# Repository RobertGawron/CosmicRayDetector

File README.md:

# CosmicRayDetector

**This project is unfinished.**

## Purpose

Cosmic radiation consists of a constant stream of high-energy particles originating from deep space. When these particles reach Earth, they collide with atoms in the atmosphere, producing a variety of secondary particles, one of which is the muon. This device is designed to detect these muons using a grid of Geiger tubes, while distinguishing them from Earth's natural background radiation. The goal is to create a more precise muon detection system using digital processing, allowing for enhanced readability and further data analysis on a PC, unlike other projects that rely on analog interfaces.

## Principle of Operation

When cosmic rays strike the Earth's atmosphere, they produce high-speed particles, such as muons, which can be detected by Geiger tubes. Due to their high energy, muons pass through Geiger tubes without being stopped, and if multiple tubes are aligned, a muon passing through one will likely pass through others, registering multiple detections. This behavior distinguishes muons from background radiation, which lacks the energy to penetrate multiple Geiger tubes.

To further reduce interference from background radiation, lead shielding is placed around the Geiger tubes. This setup allows the device to filter out low-energy radioactive particles from Earth's environment, isolating the detection of cosmic muons.

## Actual Hardware Version 

The device is the violet PCB. It probably doesn’t work - I can't say for sure because I forgot to buy all the components.

The story behind this device is actually quite interesting. The first version I created was a very small PCB. Depending on which components were soldered, it could be used in three different ways: as a user interface module (with a 4x4 LED grid and push buttons), to connect the GM tube on the "hot side" (connectors and a resistor to limit pulse current), or on the "cold side" (shunt resistor and ADC). It was a clever design to save money on PCB manufacturing, but it added a lot of complexity during assembly. I quickly realized that saving $10 wasn’t worth adding two hours of soldering work.

In the second version, I used NAND gates as an ADC. While I believe this setup would work, it's a bit too old-school, and it would make much more sense to use comparators instead.

The third version is currently under development.

As visible on the image, due to forgetting to buy the NAND gates, as a last resort, I attempted to use a high-to-low logic level converter with MOSFETs I had on hand. It didn’t work, and I didn’t have time to investigate further.

## System Architecture

The user interface is still to be determined.

Tools: PlantUML

## Hardware

* To generate the high voltage required by the Geiger tubes, the [DC/DC converter from this Geiger-Müller counter project](https://github.com/RobertGawron/GeigerMullerCounter) is utilized.
* The Geiger tube model used is the Soviet STS-5 (СТС-5).

Tools: KiCad (for PCB design).

## Software

Software doesn't exists yet.

* The FPGA (Cyclone IV) firmware will be written in Verilog using Quartus Lite as the IDE.
* See [Setting up the development environment on Windows](./wiki/Setting-up-development-environment-on-Windows) for more details.

## Hazards

**Warning: The device operates at high voltage, which can cause serious injury or death. Avoid touching the PCB or Geiger tubes while the device is powered on.**

## License
This project is licensed under the MIT License. See the [LICENSE](./LICENSE) file for details.

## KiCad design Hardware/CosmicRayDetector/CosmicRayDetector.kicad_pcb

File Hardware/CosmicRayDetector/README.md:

# CosmicRayDetector

To reduce manufacturing costs, one PCB was designed all modules. This PCB used in three variants:

- **A/D converter** - four pieces, each for each row of GM Tubes. Mount **only** components visible on  GMTubeConnector.sch, HVConnector.sch
- **Connector between GM tube and high voltage generator** - four pieces, each for ach row of GM Tubes. Mount **only** components visible on **only**  GMTubeConnector.sch, ADC.sch, PowerSupply.sch
- **User interface** - one piece. Mount **only** components visible onUserInterface.sch PowerSupply.sch

In total, nine PCBs are needed.

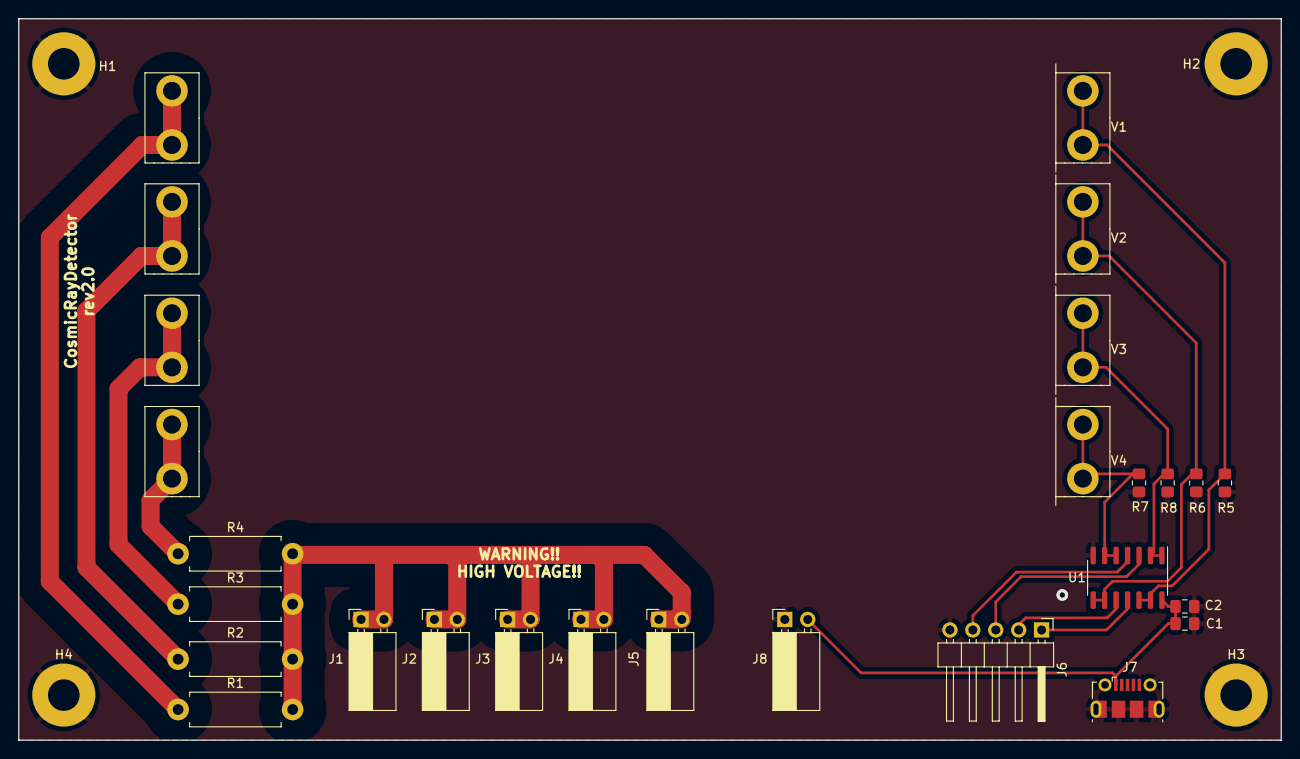
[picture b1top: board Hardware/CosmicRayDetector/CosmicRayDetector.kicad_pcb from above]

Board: 2 copper layers, 140.0 x 80.0 mm, 27 parts (0 on the bottom side), 15 nets.

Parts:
C1, C2: 100n; C_0805_2012Metric_Pad1.18x1.45mm_HandSolder
H1, H2, H3, H4: MountingHole_Pad; MountingHole_3.5mm_Pad
J1, J2, J3, J4, J5, J8: Conn_01x02_Pin; PinSocket_1x02_P2.54mm_Horizontal
J6: Conn_01x05_Socket; PinHeader_1x05_P2.54mm_Horizontal
J7: USB_B_Micro; USB_Micro-B_Molex-105017-0001
R1, R2, R3, R4: 5M1; R_Axial_DIN0411_L9.9mm_D3.6mm_P12.70mm_Horizontal
R5, R6, R7, R8: 10k; R_0805_2012Metric_Pad1.20x1.40mm_HandSolder
U1: HEF4093B; SOIC-14_3.9x8.7mm_P1.27mm
V1, V2, V3, V4: Nuclear-Radiation_Detector; GeigerTube

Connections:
+5V: C1.1, C2.1, J7.1 (VBUS), J8.2, U1.14 (VCC)
GND: C1.2, C2.2, H1.1, H2.1, H3.1, H4.1, J6.5, J7.5 (GND), J7.6 (Shield), J8.1, R5.2, R6.2, R7.2, R8.2, U1.7 (GND)
unnamed: J1.1, J1.2, J2.1, J2.2, J3.1, J3.2, J4.1, J4.2, J5.1, J5.2, R1.2, R2.2, R3.2, R4.2
unnamed: J6.1, U1.11
unnamed: J6.2, U1.10
unnamed: J6.3, U1.3
unnamed: J6.4, U1.4
unnamed: R1.1, V1.2
unnamed: R2.1, V2.2
unnamed: R3.1, V3.2
unnamed: R4.1, V4.2
unnamed: R5.1, U1.12, U1.13, V1.1
unnamed: R6.1, U1.8, U1.9, V2.1
unnamed: R7.1, U1.5, U1.6, V4.1
unnamed: R8.1, U1.1, U1.2, V3.1

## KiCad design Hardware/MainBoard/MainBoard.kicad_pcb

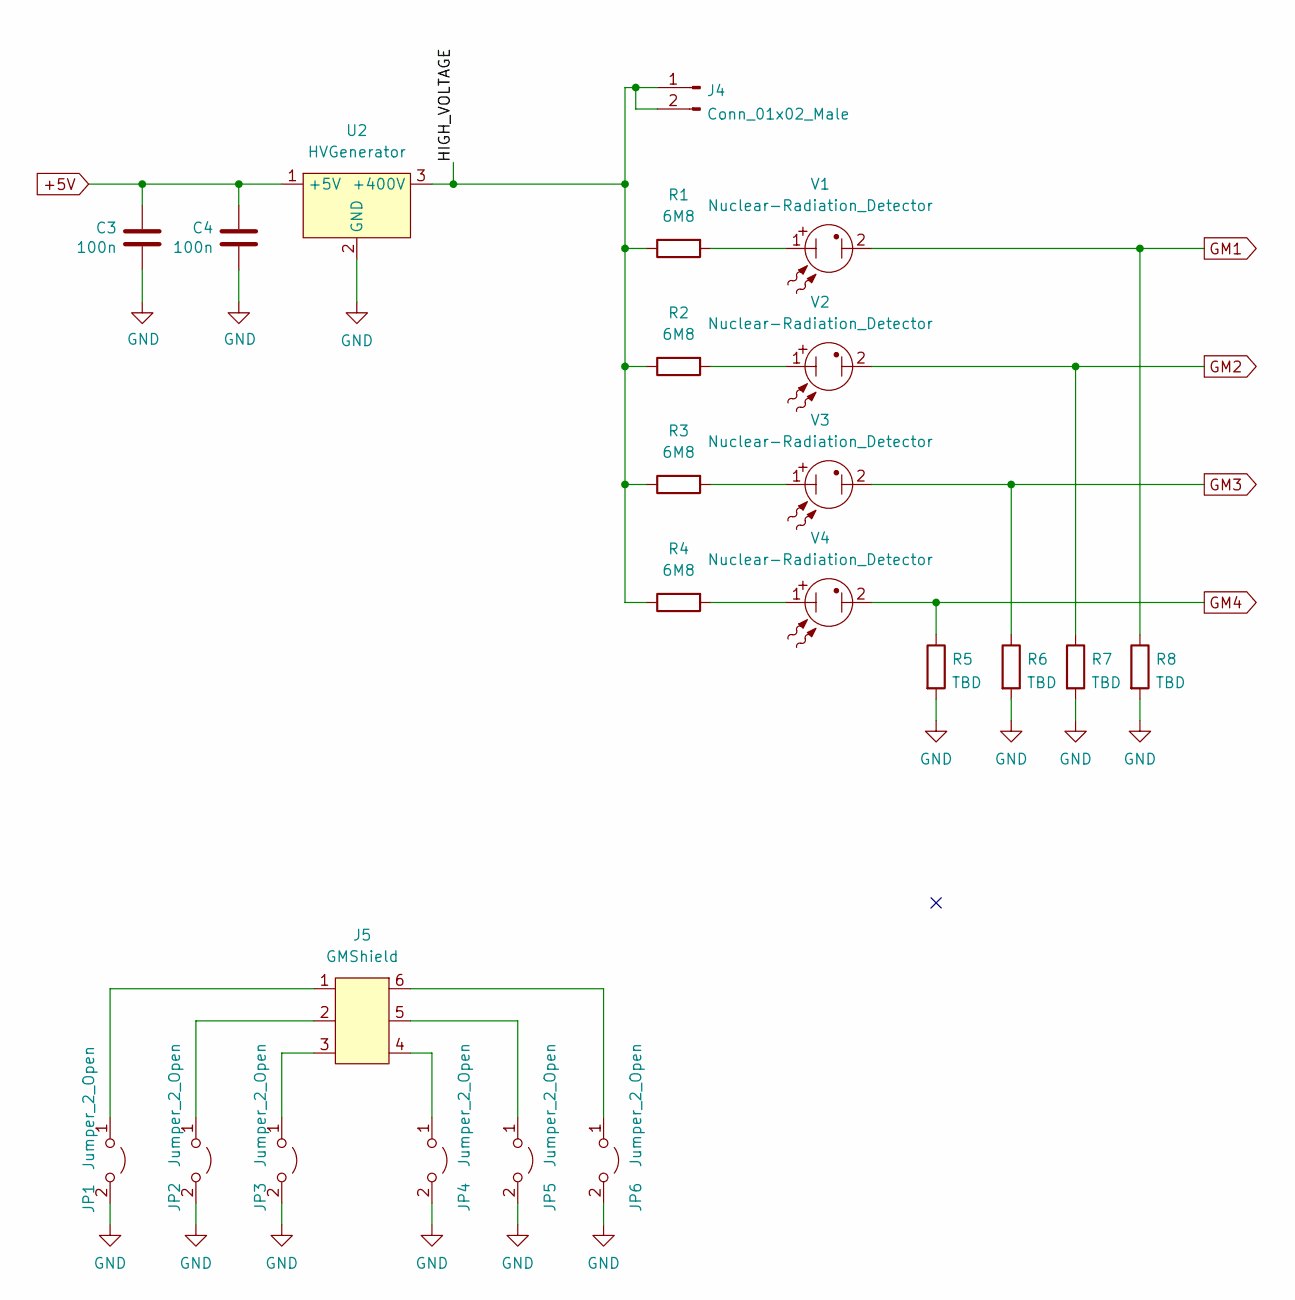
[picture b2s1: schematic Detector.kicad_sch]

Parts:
C3, C4: 100n; C_0805_2012Metric
J4: Conn_01x02_Male; PinHeader_1x02_P2.54mm_Horizontal
J5: GMShield
JP1, JP2, JP3, JP4, JP5, JP6: Jumper_2_Open; SolderJumper-2_P1.3mm_Open_Pad1.0x1.5mm
R1, R2, R3, R4: 6M8; R_Axial_DIN0207_L6.3mm_D2.5mm_P10.16mm_Horizontal
R5, R6, R7, R8: TBD; R_0805_2012Metric
U2: HVGenerator
V1, V2, V3, V4: Nuclear-Radiation_Detector; GeigerTubeConnector

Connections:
+5V: C3.1, C4.1, U2.1 (+5V); also elsewhere on the board
/Detector/HIGH_VOLTAGE: J4.1, J4.2, R1.1, R2.1, R3.1, R4.1, U2.3 (+400V)
GM1: R8.1, V1.2; also elsewhere on the board
GM2: R7.1, V2.2; also elsewhere on the board
GM3: R6.1, V3.2; also elsewhere on the board
GM4: R5.1, V4.2; also elsewhere on the board
GND: C3.2, C4.2, JP1.2 (B), JP2.2 (B), JP3.2 (B), JP4.2 (B), JP5.2 (B), JP6.2 (B), R5.2, R6.2, R7.2, R8.2, U2.2 (GND); also elsewhere on the board
unnamed: J5.1, JP1.1 (A)
unnamed: J5.2, JP2.1 (A)
unnamed: J5.3, JP3.1 (A)
unnamed: J5.4, JP4.1 (A)
unnamed: J5.5, JP5.1 (A)
unnamed: J5.6, JP6.1 (A)
unnamed: R1.2, V1.1
unnamed: R2.2, V2.1
unnamed: R3.2, V3.1
unnamed: R4.2, V4.1

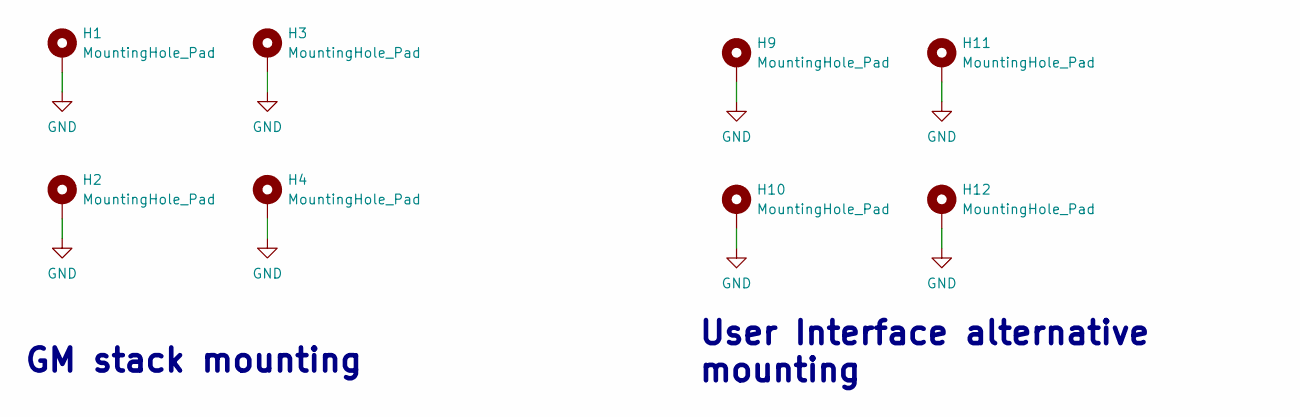
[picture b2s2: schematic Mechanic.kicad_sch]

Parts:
H1, H2, H3, H4, H9, H10, H11, H12: MountingHole_Pad; MountingHole_3.2mm_M3_DIN965_Pad

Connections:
GND: H1.1, H2.1, H3.1, H4.1, H9.1, H10.1, H11.1, H12.1; also elsewhere on the board

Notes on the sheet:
GM stack mounting
User Interface alternative mounting

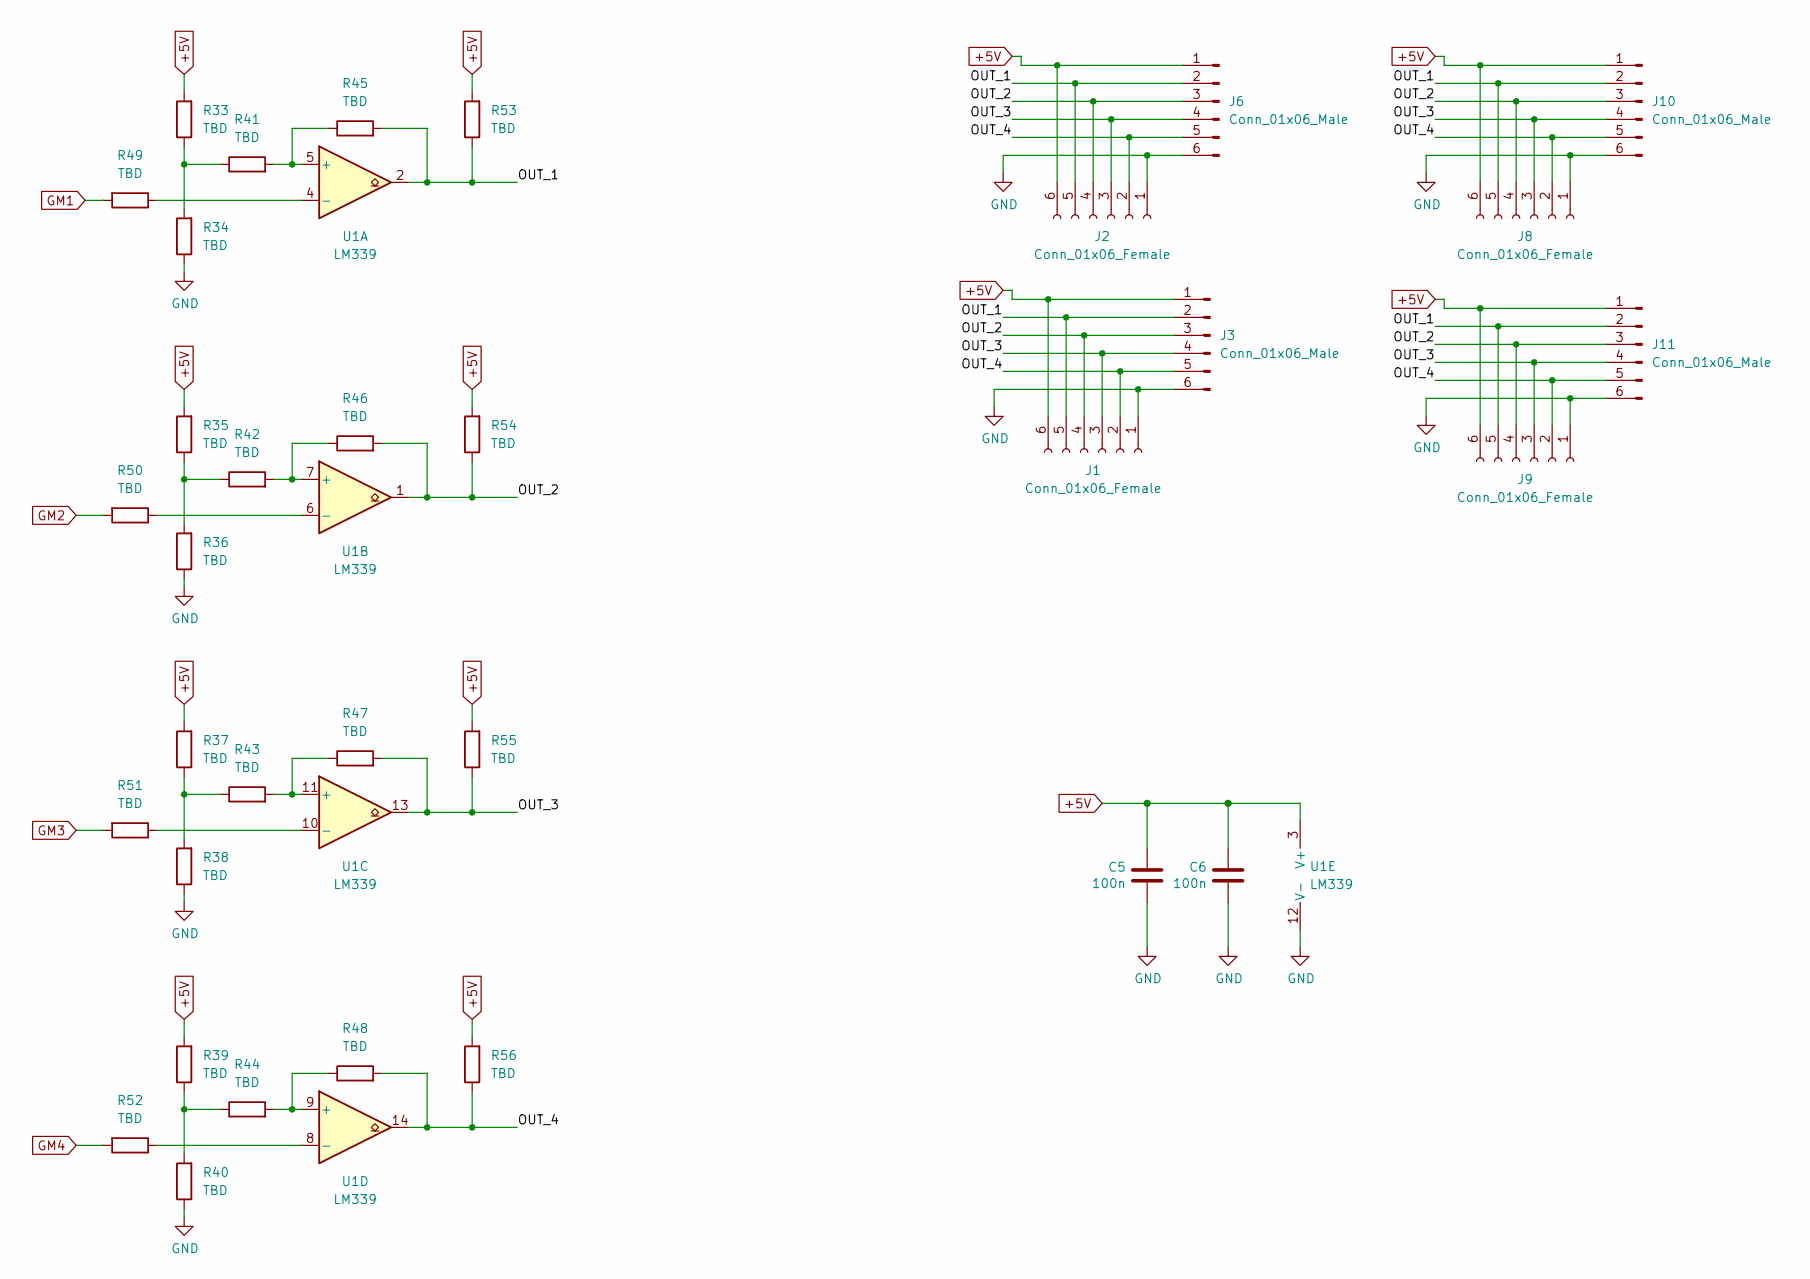
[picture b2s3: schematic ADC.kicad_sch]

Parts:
C5, C6: 100n; C_0805_2012Metric
J1, J2, J8, J9: Conn_01x06_Female; PinSocket_1x06_P2.54mm_Vertical_SMD_Pin1Left
J3, J6, J10, J11: Conn_01x06_Male; PinHeader_1x06_P2.54mm_Vertical_SMD_Pin1Left
R33, R34, R35, R36, R37, R38, R39, R40, R41, R42, R43, R44, R45, R46, R47, R48, R49, R50, R51, R52, R53, R54, R55, R56: TBD; R_0805_2012Metric
U1: LM339; SO-14_3.9x8.65mm_P1.27mm

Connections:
+5V: C5.1, C6.1, J1.6, J2.6, J3.1, J6.1, J8.6, J9.6, J10.1, J11.1, R33.2, R35.2, R37.2, R39.2, R53.2, R54.2, R55.2, R56.2, U1.3 (V+); also elsewhere on the board
/ADC/OUT_1: J1.5, J2.5, J3.2, J6.2, J8.5, J9.5, J10.2, J11.2, R45.2, R53.1, U1.2
/ADC/OUT_2: J1.4, J2.4, J3.3, J6.3, J8.4, J9.4, J10.3, J11.3, R46.2, R54.1, U1.1
/ADC/OUT_3: J1.3, J2.3, J3.4, J6.4, J8.3, J9.3, J10.4, J11.4, R47.2, R55.1, U1.13
/ADC/OUT_4: J1.2, J2.2, J3.5, J6.5, J8.2, J9.2, J10.5, J11.5, R48.2, R56.1, U1.14
GM1: R49.2; also elsewhere on the board
GM2: R50.2; also elsewhere on the board
GM3: R51.2; also elsewhere on the board
GM4: R52.2; also elsewhere on the board
GND: C5.2, C6.2, J1.1, J2.1, J3.6, J6.6, J8.1, J9.1, J10.6, J11.6, R34.1, R36.1, R38.1, R40.1, U1.12 (V-); also elsewhere on the board
unnamed: R33.1, R34.2, R41.1
unnamed: R35.1, R36.2, R42.1
unnamed: R37.1, R38.2, R43.1
unnamed: R39.1, R40.2, R44.1
unnamed: R49.1, U1.4 (-)
unnamed: R41.2, R45.1, U1.5 (+)
unnamed: R50.1, U1.6 (-)
unnamed: R42.2, R46.1, U1.7 (+)
unnamed: R52.1, U1.8 (-)
unnamed: R44.2, R48.1, U1.9 (+)
unnamed: R51.1, U1.10 (-)
unnamed: R43.2, R47.1, U1.11 (+)

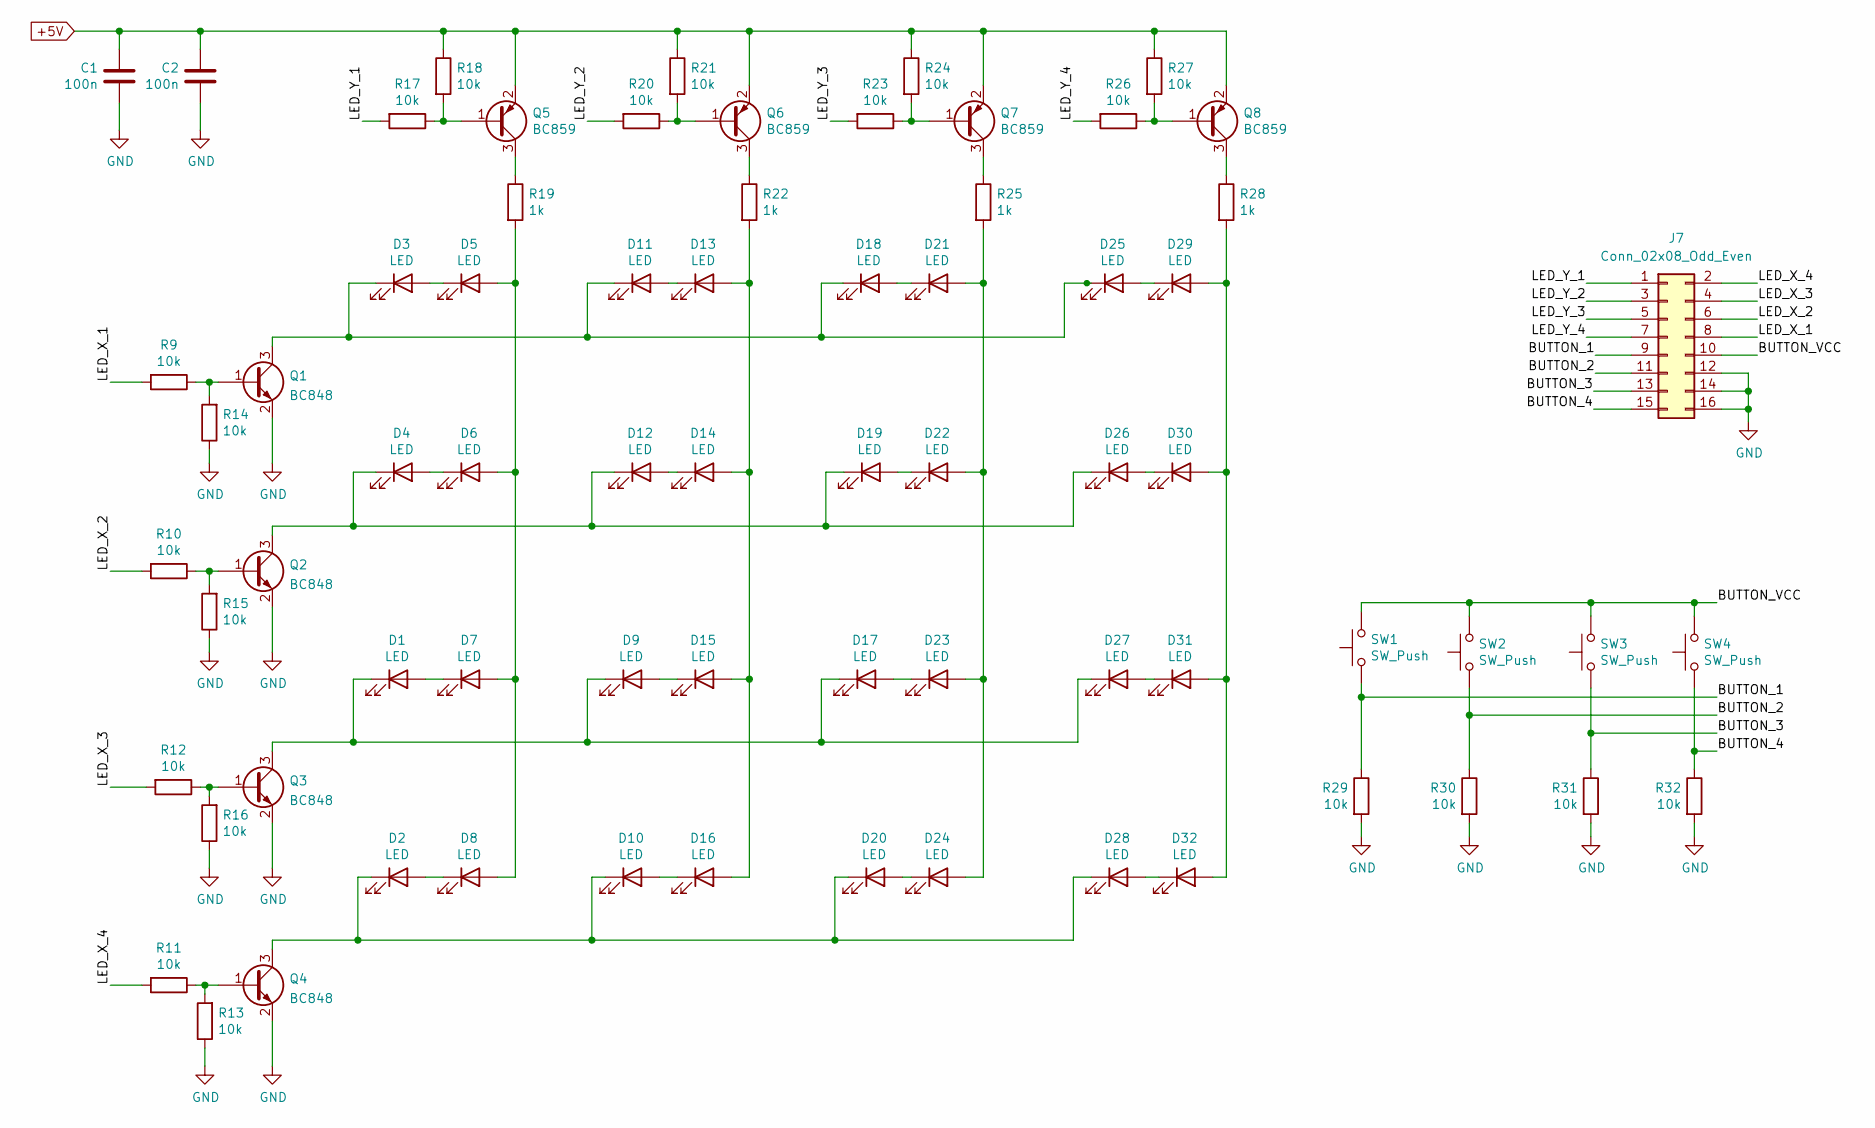
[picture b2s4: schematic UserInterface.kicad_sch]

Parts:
C1, C2: 100n; C_0805_2012Metric
D1, D2, D3, D4, D5, D6, D7, D8, D9, D10, D11, D12, D13, D14, D15, D16, D17, D18, D19, D20, D21, D22, D23, D24, D25, D26, D27, D28, D29, D30, D31, D32: LED; LED_1206_3216Metric
J7: Conn_02x08_Odd_Even; PinHeader_2x08_P2.54mm_Vertical
Q1, Q2, Q3, Q4: BC848; SOT-23
Q5, Q6, Q7, Q8: BC859; SOT-23
R9, R10, R11, R12, R13, R14, R15, R16, R17, R18, R20, R21, R23, R24, R26, R27, R29, R30, R31, R32: 10k; R_0805_2012Metric
R19, R22, R25, R28: 1k; R_0805_2012Metric
SW1, SW2, SW3, SW4: SW_Push; SW_PUSH_6mm

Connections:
+5V: C1.1, C2.1, Q5.2 (E), Q6.2 (E), Q7.2 (E), Q8.2 (E), R18.1, R21.1, R24.1, R27.1; also elsewhere on the board
/UserInterface/BUTTON_1: J7.9, R29.1, SW1.1
/UserInterface/BUTTON_2: J7.11, R30.1, SW2.1
/UserInterface/BUTTON_3: J7.13, R31.1, SW3.1
/UserInterface/BUTTON_4: J7.15, R32.1, SW4.1
/UserInterface/BUTTON_VCC: J7.10, SW1.2, SW2.2, SW3.2, SW4.2
/UserInterface/LED_X_1: J7.8, R9.2
/UserInterface/LED_X_2: J7.6, R10.2
/UserInterface/LED_X_3: J7.4, R12.2
/UserInterface/LED_X_4: J7.2, R11.2
/UserInterface/LED_Y_1: J7.1, R17.2
/UserInterface/LED_Y_2: J7.3, R20.2
/UserInterface/LED_Y_3: J7.5, R23.2
/UserInterface/LED_Y_4: J7.7, R26.2
GND: C1.2, C2.2, J7.12, J7.14, J7.16, Q1.2 (E), Q2.2 (E), Q3.2 (E), Q4.2 (E), R13.1, R14.1, R15.1, R16.1, R29.2, R30.2, R31.2, R32.2; also elsewhere on the board
unnamed: D1.1 (K), D9.1 (K), D17.1 (K), D27.1 (K), Q3.3 (C)
unnamed: D1.2 (A), D7.1 (K)
unnamed: D2.2 (A), D8.1 (K)
unnamed: D3.2 (A), D5.1 (K)
unnamed: D4.2 (A), D6.1 (K)
unnamed: D5.2 (A), D6.2 (A), D7.2 (A), D8.2 (A), R19.2
unnamed: D2.1 (K), D10.1 (K), D20.1 (K), D28.1 (K), Q4.3 (C)
unnamed: D10.2 (A), D16.1 (K)
unnamed: D3.1 (K), D11.1 (K), D18.1 (K), D25.1 (K), Q1.3 (C)
unnamed: D11.2 (A), D13.1 (K)
unnamed: D4.1 (K), D12.1 (K), D19.1 (K), D26.1 (K), Q2.3 (C)
unnamed: D12.2 (A), D14.1 (K)
unnamed: D13.2 (A), D14.2 (A), D15.2 (A), D16.2 (A), R22.2
unnamed: D9.2 (A), D15.1 (K)
unnamed: D17.2 (A), D23.1 (K)
unnamed: D18.2 (A), D21.1 (K)
unnamed: D19.2 (A), D22.1 (K)
unnamed: D20.2 (A), D24.1 (K)
unnamed: D21.2 (A), D22.2 (A), D23.2 (A), D24.2 (A), R25.2
unnamed: D25.2 (A), D29.1 (K)
unnamed: D26.2 (A), D30.1 (K)
unnamed: D27.2 (A), D31.1 (K)
unnamed: D28.2 (A), D32.1 (K)
unnamed: D29.2 (A), D30.2 (A), D31.2 (A), D32.2 (A), R28.2
unnamed: Q1.1 (B), R9.1, R14.2
unnamed: Q2.1 (B), R10.1, R15.2
unnamed: Q3.1 (B), R12.1, R16.2
unnamed: Q4.1 (B), R11.1, R13.2
unnamed: Q5.1 (B), R17.1, R18.2
unnamed: Q5.3 (C), R19.1
unnamed: Q6.1 (B), R20.1, R21.2
unnamed: Q6.3 (C), R22.1
unnamed: Q7.1 (B), R23.1, R24.2
unnamed: Q7.3 (C), R25.1
unnamed: Q8.1 (B), R26.1, R27.2
unnamed: Q8.3 (C), R28.1

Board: 2 copper layers, 137 parts (0 on the bottom side), 82 nets, no tracks yet.

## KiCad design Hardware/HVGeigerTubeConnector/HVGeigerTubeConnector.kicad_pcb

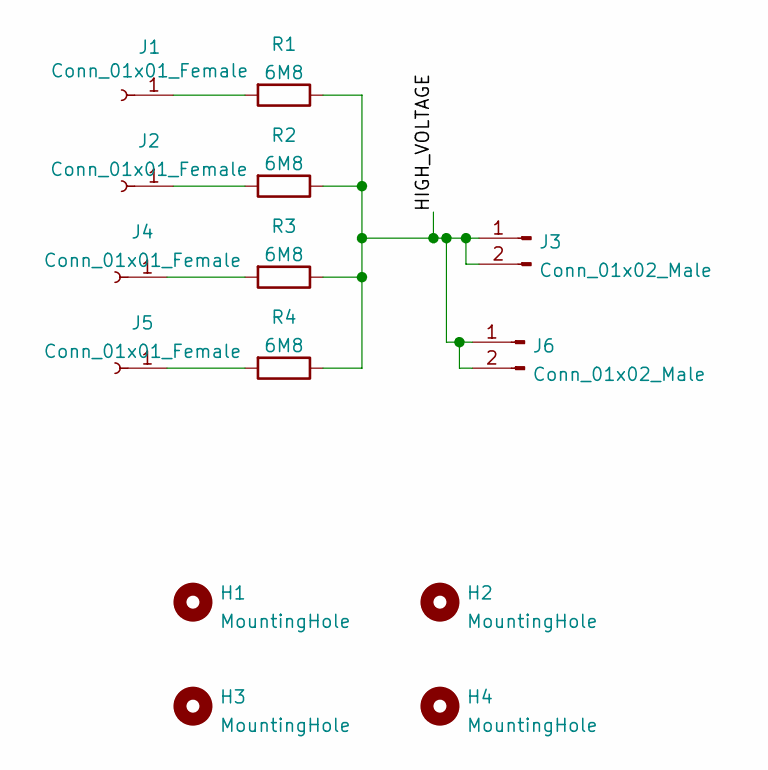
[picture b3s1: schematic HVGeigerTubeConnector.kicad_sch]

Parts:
H1, H2, H3, H4: MountingHole; MountingHole_3.5mm
J1, J2, J4, J5: Conn_01x01_Female; GeigerTubeConnector
J3, J6: Conn_01x02_Male; PinHeader_1x02_P2.54mm_Horizontal
R1, R2, R3, R4: 6M8; R_Axial_DIN0207_L6.3mm_D2.5mm_P10.16mm_Horizontal

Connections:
/HIGH_VOLTAGE: J3.1, J3.2, J6.1, J6.2, R1.1, R2.1, R3.1, R4.1
unnamed: J1.1, R1.2
unnamed: J2.1, R2.2
unnamed: J4.1, R3.2
unnamed: J5.1, R4.2

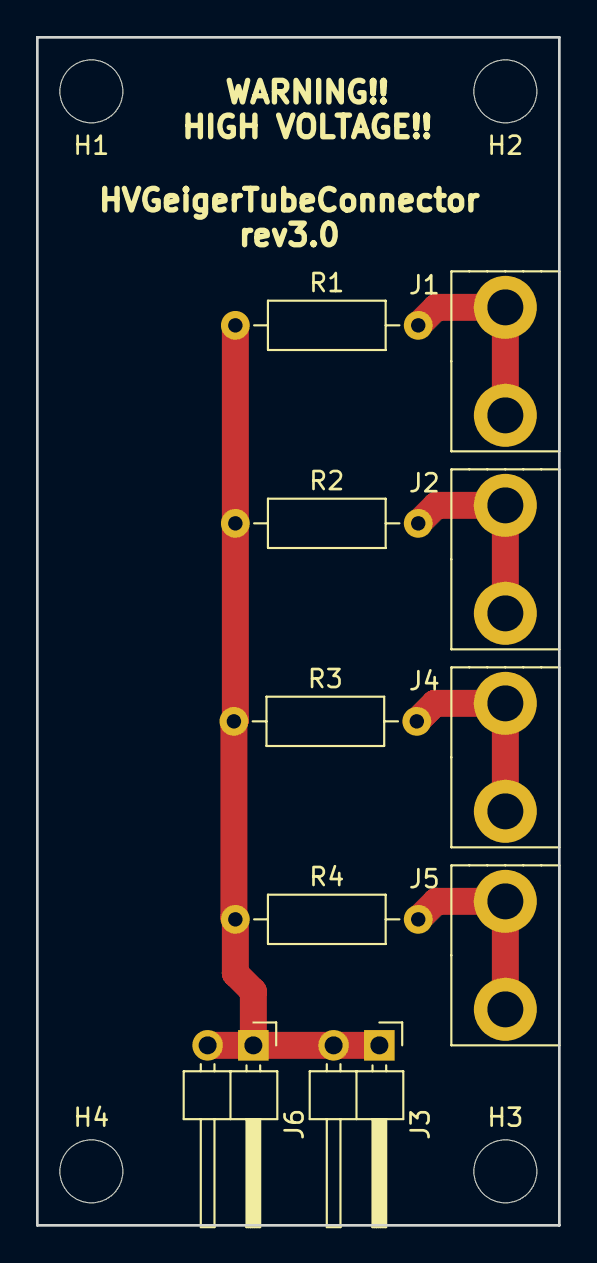
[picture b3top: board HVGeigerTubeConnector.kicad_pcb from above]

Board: 2 copper layers, 29.0 x 66.0 mm, 14 parts (0 on the bottom side), 5 nets.

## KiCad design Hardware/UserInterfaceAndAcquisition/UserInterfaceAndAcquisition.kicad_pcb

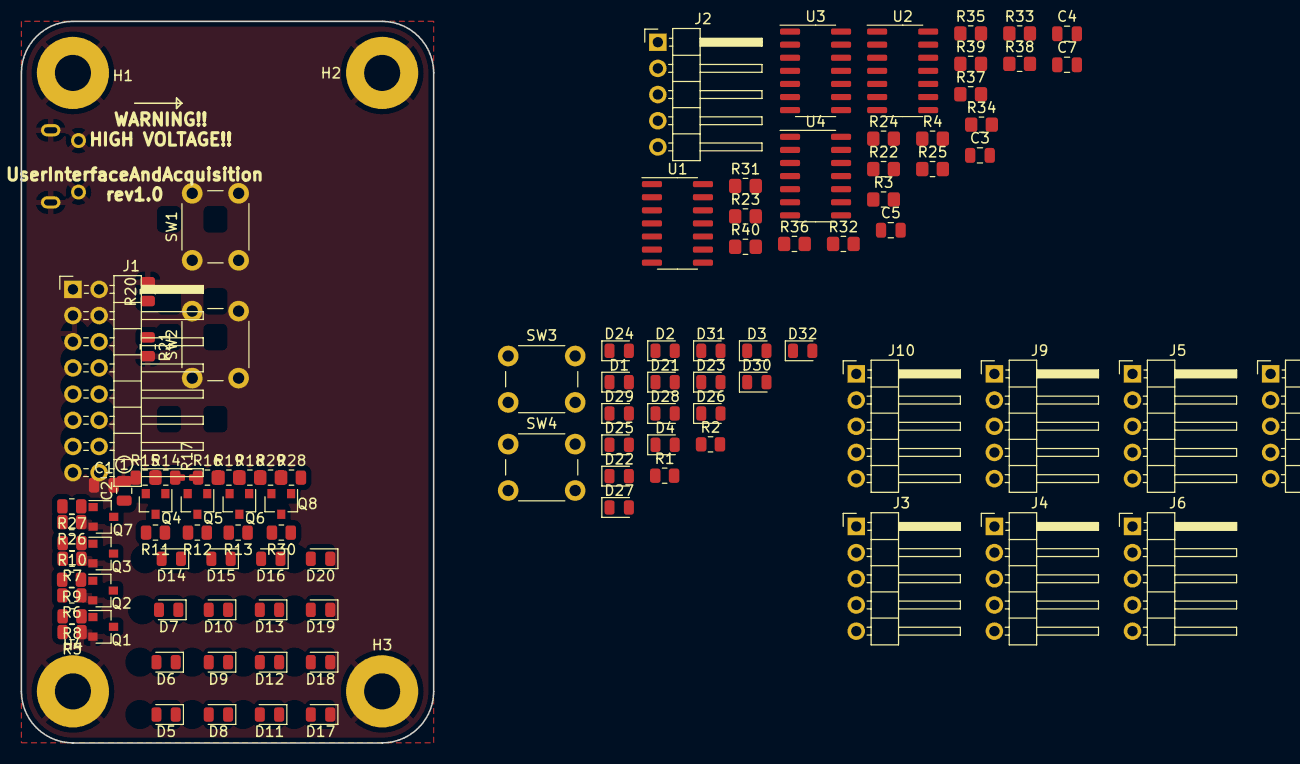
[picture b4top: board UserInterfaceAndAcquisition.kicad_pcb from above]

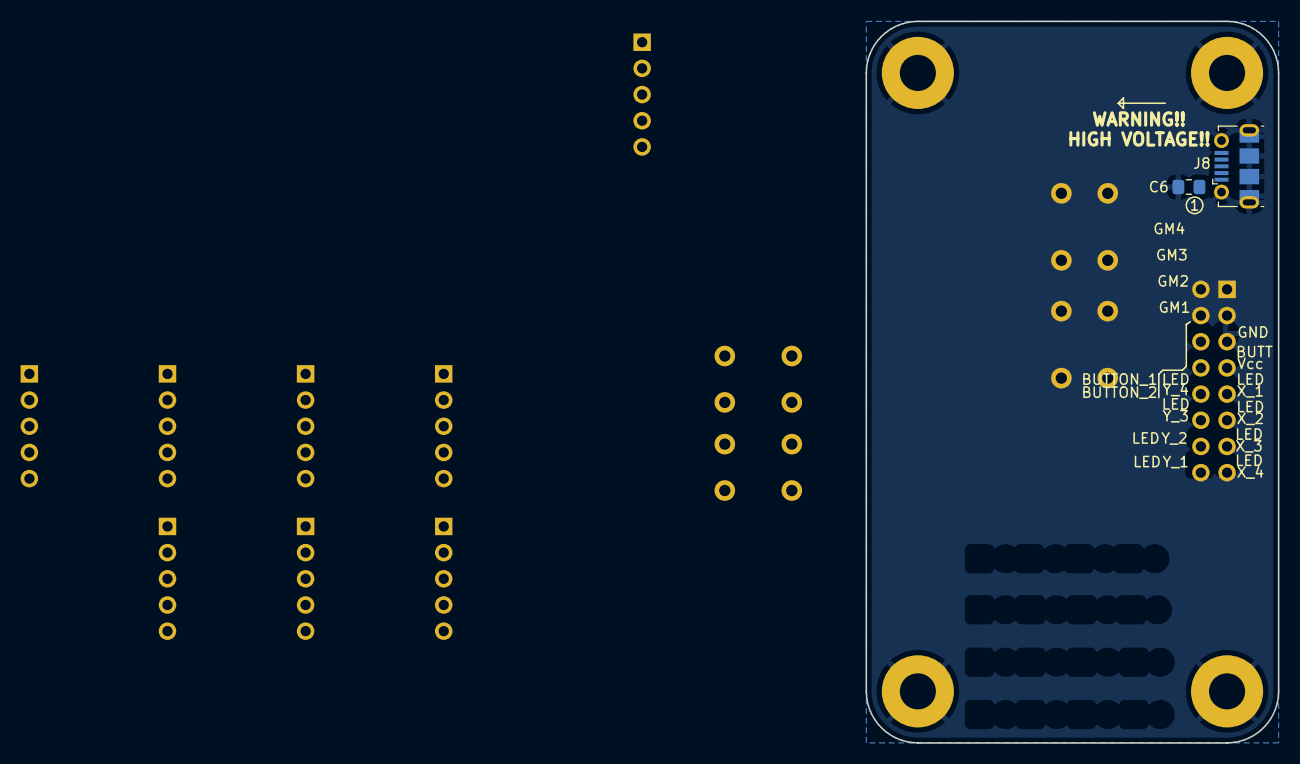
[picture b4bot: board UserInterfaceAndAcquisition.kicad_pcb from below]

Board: 2 copper layers, 40.0 x 70.0 mm, 109 parts (2 on the bottom side), 68 nets, no tracks yet.

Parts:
C1, C2, C3, C4, C5, C7: 100n; C_0805_2012Metric
C6: 100n; C_0805_2012Metric_Pad1.15x1.40mm_HandSolder
D1, D2, D3, D4, D5, D6, D7, D8, D9, D10, D11, D12, D13, D14, D15, D16, D17, D18, D19, D20, D21, D22, D23, D24, D25, D26, D27, D28, D29, D30, D31, D32: LED; LED_0805_2012Metric
H1, H2, H3, H4: MountingHole_Pad; MountingHole_3.5mm_Pad
J1: Conn_02x08_Odd_Even; PinHeader_2x08_P2.54mm_Horizontal
J2, J3, J4, J5, J6, J7, J9, J10: Conn_01x05_Male; PinHeader_1x05_P2.54mm_Horizontal
J8: USB_B_Micro; USB_Micro-B_Molex-105017-0001
Q1, Q2, Q3, Q7: BC848; SOT-23
Q4, Q5, Q6, Q8: BC859; SOT-23
R1, R2, R5, R6, R7, R8, R9, R10, R14, R15, R16, R18, R19, R20, R21, R26, R27, R28, R29: 10k; R_0805_2012Metric
R3, R4, R22, R23, R24, R25, R31, R32, R33, R34, R35, R36, R37, R38, R39, R40: 10k; R_0805_2012Metric_Pad1.20x1.40mm_HandSolder
R11, R12, R13, R30: 1k; R_0805_2012Metric
R17: 10k; R_0402_1005Metric
SW1, SW2, SW3, SW4: SW_Push; SW_PUSH_6mm
U1, U2, U3, U4: HEF4093B; SOIC-14_3.9x8.7mm_P1.27mm

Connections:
+5V: C1.1, C2.1, Q4.2 (E), Q5.2 (E), Q6.2 (E), Q8.2 (E), R15.1, R17.1, R19.1, R29.1
/Acquisition/GM_1_1: J2.1, R22.1, U3.1, U3.2
/Acquisition/GM_1_2: J2.2, R31.1, U3.5, U3.6
/Acquisition/GM_1_3: J2.3, R35.1, U3.8, U3.9
/Acquisition/GM_1_4: J2.4, R39.1, U3.12, U3.13
/Acquisition/GM_2_1: J5.1, R4.1, U2.1, U2.2
/Acquisition/GM_2_2: J5.2, R25.1, U2.5, U2.6
/Acquisition/GM_2_3: J5.3, R34.1, U2.8, U2.9
/Acquisition/GM_2_4: J5.4, R38.1, U2.12, U2.13
/Acquisition/GM_3_1: J7.1, R23.1, U4.1, U4.2
/Acquisition/GM_3_2: J7.2, R32.1, U4.5, U4.6
/Acquisition/GM_3_3: J7.3, R36.1, U4.8, U4.9
/Acquisition/GM_3_4: J7.4, R40.1, U4.12, U4.13
/Acquisition/GM_4_1: J10.1, R3.1, U1.1, U1.2
/Acquisition/GM_4_2: J10.2, R24.1, U1.5, U1.6
/Acquisition/GM_4_3: J10.3, R33.1, U1.8, U1.9
/Acquisition/GM_4_4: J10.4, R37.1, U1.12, U1.13
/UserInterface/BUTTON_1: J1.9, R20.1, SW1.1
/UserInterface/BUTTON_2: J1.11, R21.1, SW2.1
/UserInterface/BUTTON_3: J1.13, R1.1, SW3.1
/UserInterface/BUTTON_4: J1.15, R2.1, SW4.1
/UserInterface/BUTTON_VCC: J1.10, SW1.2, SW2.2, SW3.2, SW4.2
/UserInterface/LED_X_1: J1.8, R8.2
/UserInterface/LED_X_2: J1.6, R9.2
/UserInterface/LED_X_3: J1.4, R10.2
/UserInterface/LED_X_4: J1.2, R27.2
/UserInterface/LED_Y_1: J1.1, R14.2
/UserInterface/LED_Y_2: J1.3, R16.2
/UserInterface/LED_Y_3: J1.5, R18.2
/UserInterface/LED_Y_4: J1.7, R28.2
GND: C1.2, C2.2, C3.2, C4.2, C5.2, C6.2, C7.2, H1.1, H2.1, H3.1, H4.1, J1.12, J1.14, J1.16, J2.5, J3.5, J4.5, J5.5, J6.5, J7.5, J8.5 (GND), J8.6 (Shield), J9.5, J10.5, Q1.2 (E), Q2.2 (E), Q3.2 (E), Q7.2 (E), R1.2, R2.2, R3.2, R4.2, R5.1, R6.1, R7.1, R20.2, R21.2, R22.2, R23.2, R24.2, R25.2, R26.1, R31.2, R32.2, R33.2, R34.2, R35.2, R36.2, R37.2, R38.2, R39.2, R40.2, U1.7 (GND), U2.7 (GND), U3.7 (GND), U4.7 (GND)
unnamed: D1.1 (K), D2.1 (K), D3.1 (K), D4.1 (K), Q1.3 (C)
unnamed: D1.2 (A), D5.1 (K)
unnamed: D2.2 (A), D8.1 (K)
unnamed: D10.1 (K), D26.2 (A)
unnamed: D8.2 (A), D9.2 (A), D10.2 (A), D15.2 (A), R12.2
unnamed: D3.2 (A), D11.1 (K)
unnamed: D11.2 (A), D12.2 (A), D13.2 (A), D16.2 (A), R13.2
unnamed: D12.1 (K), D23.2 (A)
unnamed: D13.1 (K), D27.2 (A)
unnamed: D14.1 (K), D29.2 (A)
unnamed: D5.2 (A), D6.2 (A), D7.2 (A), D14.2 (A), R11.2
unnamed: D15.1 (K), D30.2 (A)
unnamed: D16.1 (K), D31.2 (A)
unnamed: D4.2 (A), D17.1 (K)
unnamed: D17.2 (A), D18.2 (A), D19.2 (A), D20.2 (A), R30.2
unnamed: D18.1 (K), D24.2 (A)
unnamed: D19.1 (K), D28.2 (A)
unnamed: D20.1 (K), D32.2 (A)
unnamed: D21.1 (K), D22.1 (K), D23.1 (K), D24.1 (K), Q2.3 (C)
unnamed: D6.1 (K), D21.2 (A)
unnamed: D9.1 (K), D22.2 (A)
unnamed: D25.1 (K), D26.1 (K), D27.1 (K), D28.1 (K), Q3.3 (C)
unnamed: D7.1 (K), D25.2 (A)
unnamed: D29.1 (K), D30.1 (K), D31.1 (K), D32.1 (K), Q7.3 (C)
unnamed: Q1.1 (B), R5.2, R8.1
unnamed: Q2.1 (B), R6.2, R9.1
unnamed: Q3.1 (B), R7.2, R10.1
unnamed: Q4.1 (B), R14.1, R15.2
unnamed: Q4.3 (C), R11.1
unnamed: Q5.1 (B), R16.1, R17.2
unnamed: Q5.3 (C), R12.1
unnamed: Q6.1 (B), R18.1, R19.2
unnamed: Q6.3 (C), R13.1
unnamed: Q7.1 (B), R26.2, R27.1
unnamed: Q8.1 (B), R28.1, R29.2
unnamed: Q8.3 (C), R30.1
VCC: C3.1, C4.1, C5.1, C6.1, C7.1, J8.1 (VBUS), U1.14 (VCC), U2.14 (VCC), U3.14 (VCC), U4.14 (VCC)

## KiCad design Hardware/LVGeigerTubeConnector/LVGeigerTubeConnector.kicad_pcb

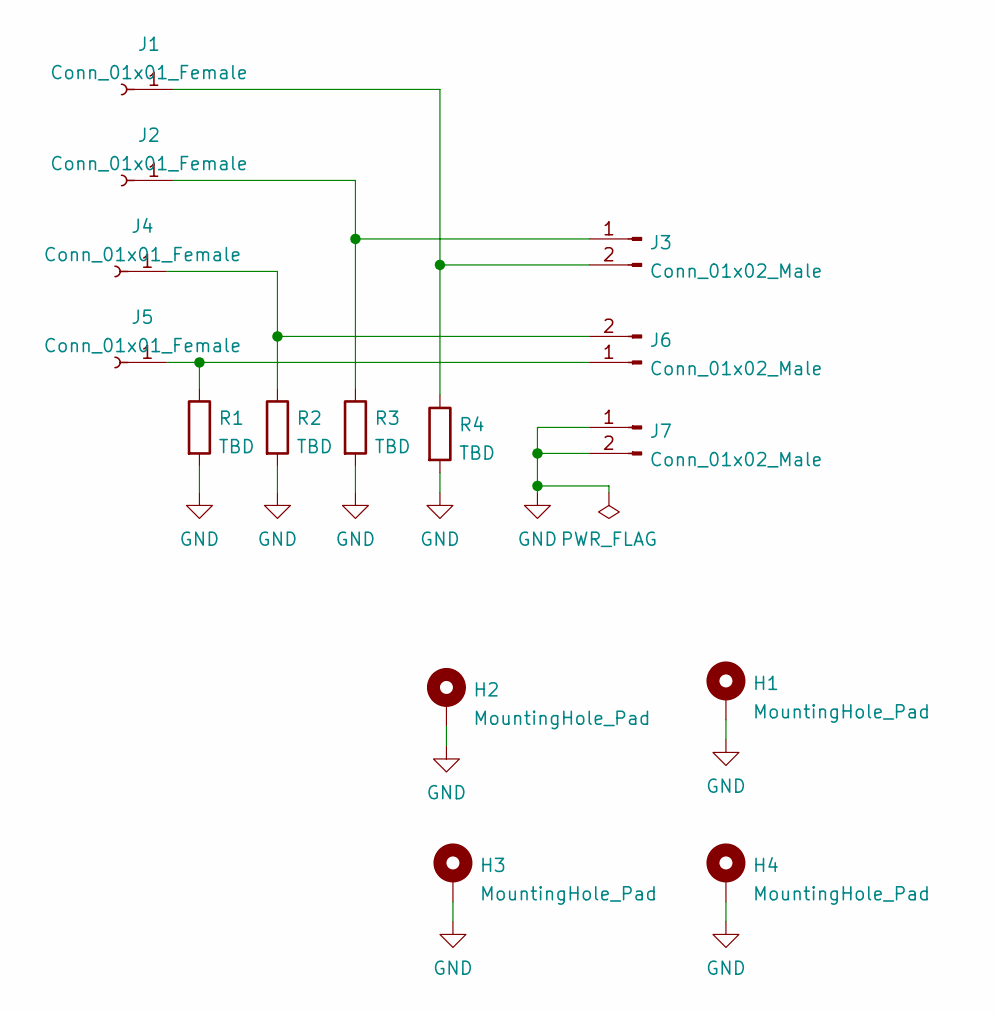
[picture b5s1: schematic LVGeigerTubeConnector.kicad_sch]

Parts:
H1, H2, H3, H4: MountingHole_Pad; MountingHole_3.5mm_Pad
J1, J2, J4, J5: Conn_01x01_Female; GeigerTubeConnector
J3, J6, J7: Conn_01x02_Male; PinHeader_1x02_P2.54mm_Horizontal
R1, R2, R3, R4: TBD; R_0805_2012Metric

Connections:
GND: H1.1, H2.1, H3.1, H4.1, J7.1, J7.2, R1.2, R2.2, R3.2, R4.2
unnamed: J1.1, J3.2, R4.1
unnamed: J2.1, J3.1, R3.1
unnamed: J4.1, J6.2, R2.1
unnamed: J5.1, J6.1, R1.1

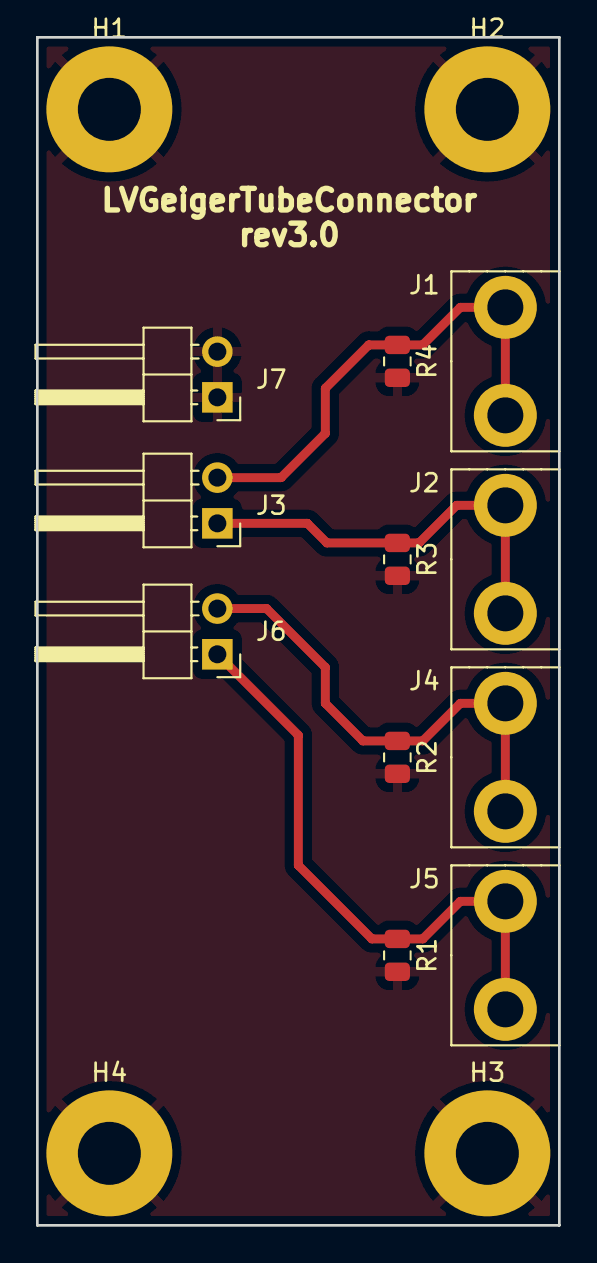
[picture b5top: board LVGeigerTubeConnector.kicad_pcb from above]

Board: 2 copper layers, 29.0 x 66.0 mm, 15 parts (0 on the bottom side), 5 nets.

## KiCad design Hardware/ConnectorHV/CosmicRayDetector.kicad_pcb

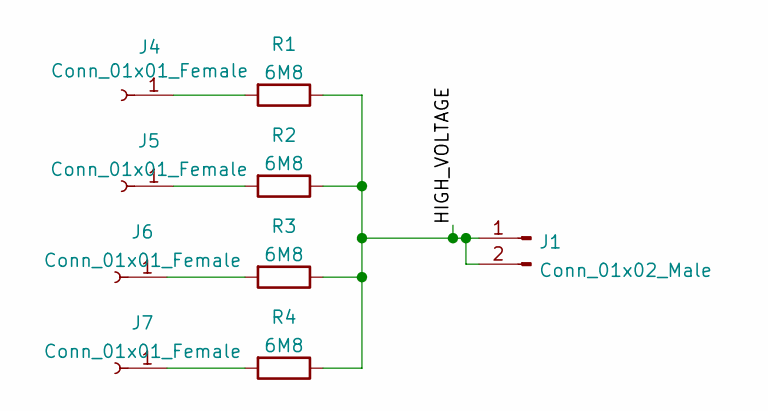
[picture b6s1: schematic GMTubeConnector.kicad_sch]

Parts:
J1: Conn_01x02_Male; PinHeader_1x02_P2.54mm_Horizontal
J4, J5, J6, J7: Conn_01x01_Female; GeigerTube
R1, R2, R3, R4: 6M8; R_Axial_DIN0207_L6.3mm_D2.5mm_P15.24mm_Horizontal

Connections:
/GMTubeConnector/HIGH_VOLTAGE: J1.1, J1.2, R1.1, R2.1, R3.1, R4.1
unnamed: J4.1, R1.2
unnamed: J5.1, R2.2
unnamed: J6.1, R3.2
unnamed: J7.1, R4.2

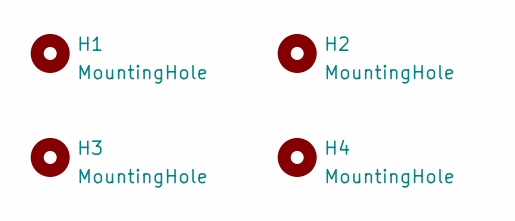
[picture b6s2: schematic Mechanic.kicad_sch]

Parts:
H1, H2, H3, H4: MountingHole; MountingHole_3.5mm

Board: 2 copper layers, 13 parts (0 on the bottom side), 5 nets, no tracks yet.
